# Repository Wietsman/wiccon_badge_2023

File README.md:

# Wiccon Badge 2023

# What is this repo: 
  This repo contains the source + firmware + PCB design for the WICCON 2023 Badge (https://wiccon.nl/) (not the SAO)

  Badge front:

  Badge back:

  The Folder PCB contains the main badge and the addon, created with KiCad.
  # Main badge
  ## Frontside
  * 4 WS2812B on the front. (made a mistake they are adressed counter clockwise)
  * 1 MODE button on the front to switch LED effects
  * 2 6 pin female connecter to attach the addon board (Cat and moon)
  * 1 SAO v1.69 (Shitty Addon) (https://hackaday.com/2019/03/20/introducing-the-shitty-add-on-v1-69bis-standard/)
  * |  PIN  |      Description      |
    |-------|-----------------------|
    | 3.3v  | Positive power supply |
    | GND   | Ground                |
    | SCL   | Not connected (sorry) |
    | SDA   | Not connected (sorry) |        
    | GPI12 | General-purpose pin   |
    | GPI13 | General-purpose pin   |    

## Backside
* ESP8622
* Powerswitch
* Reset button
* Flash button
* Batterybox
* stepdown converter (3.6-4.5v) to 3.3v
* couple of capacitor for WS2812B and stepdown converter
* 1 resistor
* lots of test pads so you can reuse the badge for other projects

## Schematic

## Usage
The badge has been designed to be reused for your project. The test pads can be used to solder anything to it and you can flash the ESP. 

You can use all the pads/pins except for (because i orderd the wrong ESP.....):
* MISO
* MOSI
* GPIO09
* GPIO10
* SCLK
* CSO

The following pins need are "special":
* GPIO00 pull to ground on boot to flash the ESP (or press flash button)
* GPIO15 is pulled to ground through a 10k resistor otherwise the ESP wont boot.

Flashing your own firmware, connect UART to tx/rx gnd power the device by battery or external 3.3v power. Hold the flash button, then press reset, release the flash button. Now you can flash your own firmware with esptool.py, arduino ide or what ever you want.

# Addon board
There are 2 addon boards for WICCON 2023, for guests (black cat and moon) and orga (purple moon, silver cat)
## Guestboard

## Orgaboard

## Schematic

## Backside

# Questions, remarks or whatever!

If you have any questions please drop me a message: 
* twitter: [twitter](https://twitter.com/wietsman)
* Website: [WBSEC.nl](https://www.wbsec.nl)

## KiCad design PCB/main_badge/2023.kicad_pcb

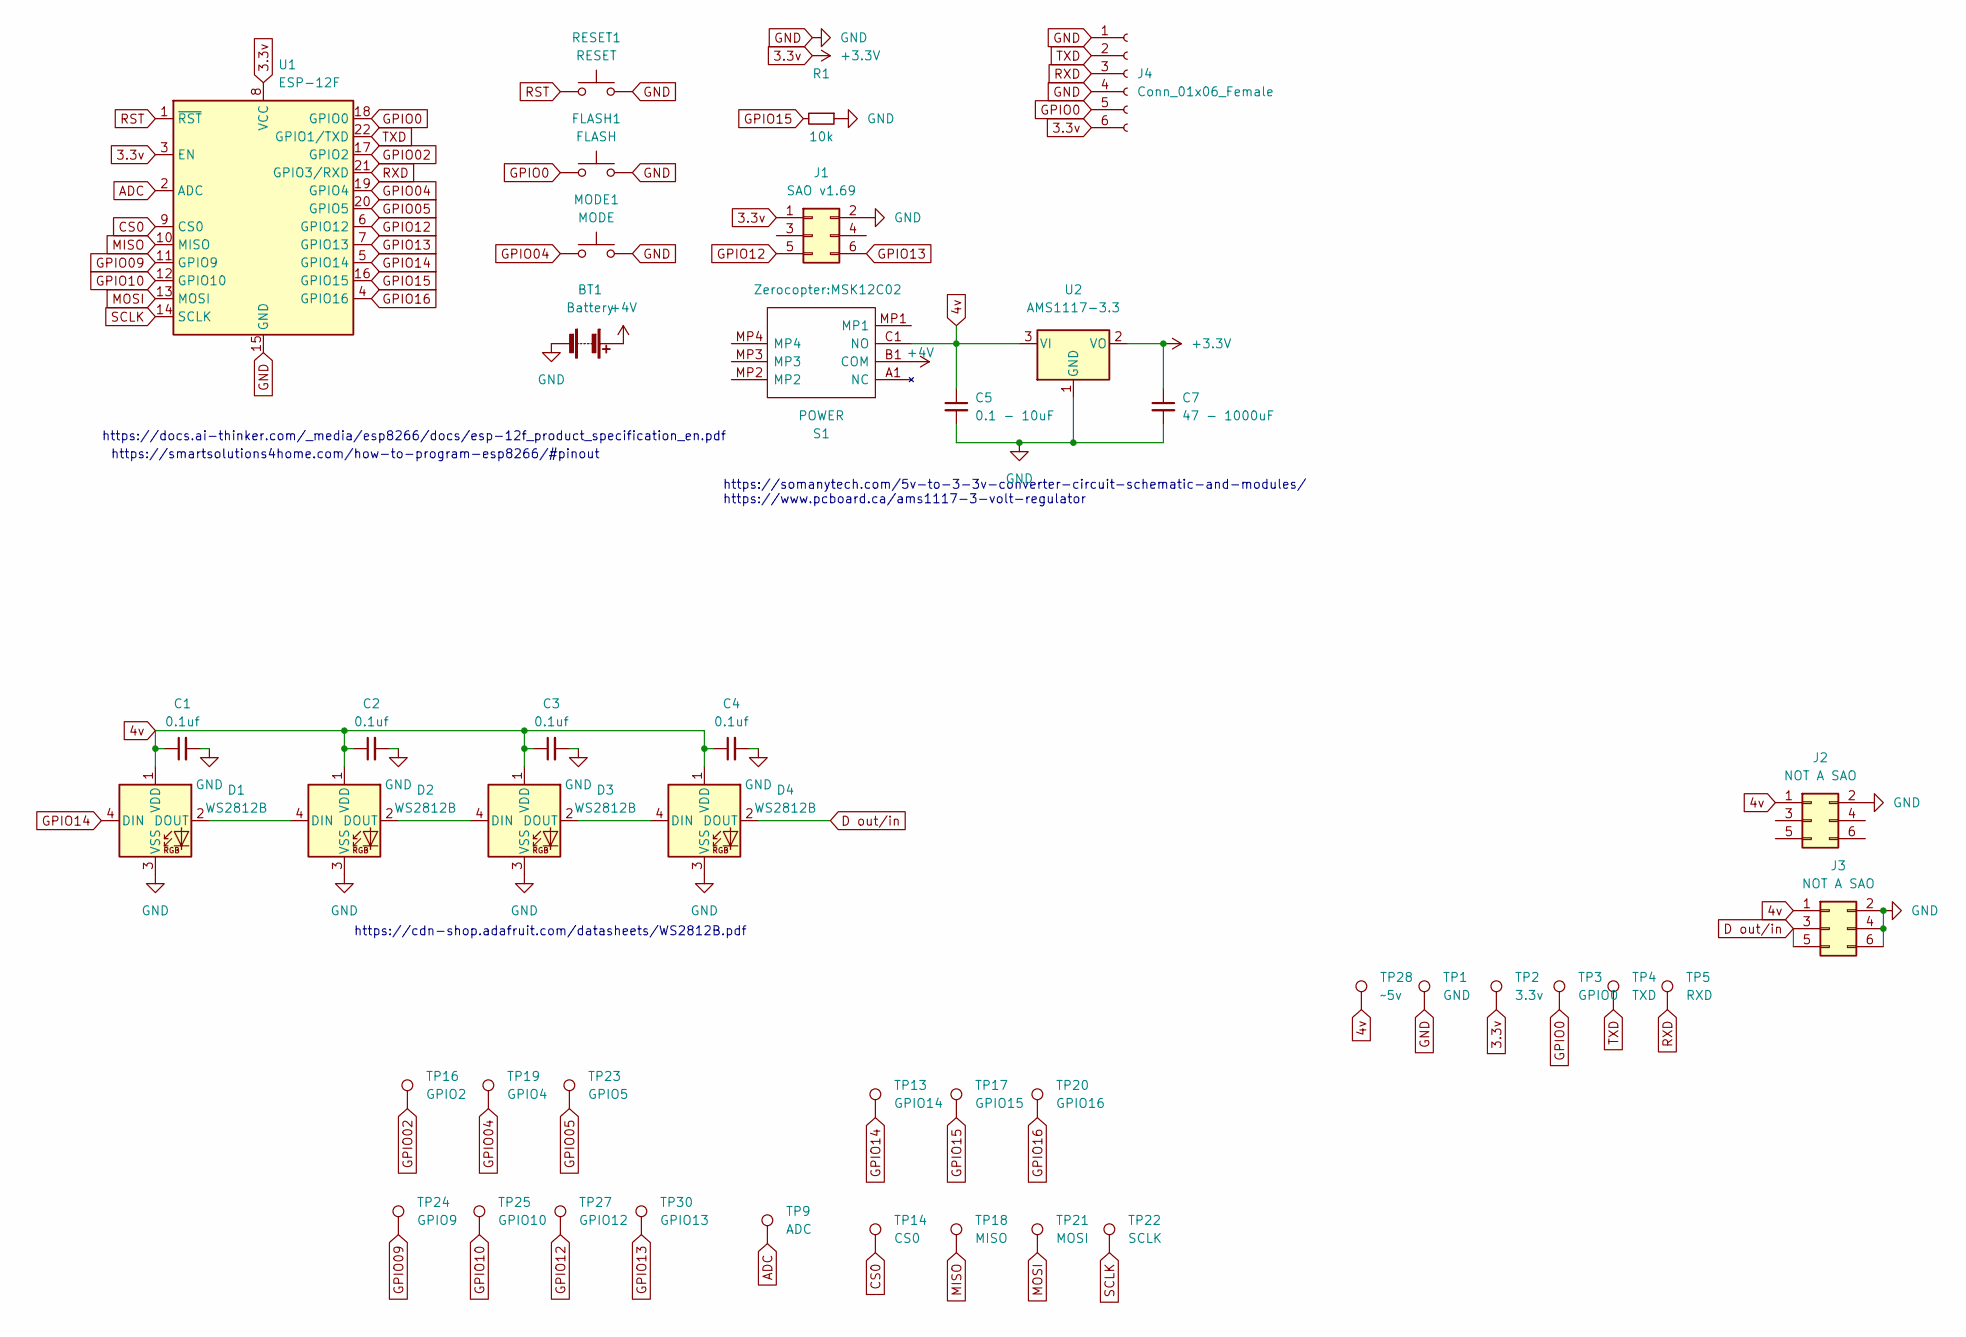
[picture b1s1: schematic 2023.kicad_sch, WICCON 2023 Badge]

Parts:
BT1: Battery; Battery_holder_3AA
C1, C2, C3, C4: 0.1uf; R_0805_2012Metric
C5: 0.1 - 10uF; C_0805_2012Metric_Pad1.18x1.45mm_HandSolder
C7: 47 - 1000uF; C_0805_2012Metric_Pad1.18x1.45mm_HandSolder
D1, D2, D3, D4: WS2812B; LED_WS2812B_PLCC4_5.0x5.0mm_P3.2mm
FLASH1: FLASH; sw_tactile_4x4
J1: SAO v1.69; PinSocket_2x03_P2.54mm_Vertical
J2, J3: NOT A SAO; PinSocket_2x03_P2.54mm_Vertical
J4: Conn_01x06_Female; Harting_har-flexicon_14110413010xxx_1x04-MP_P2.54mm_Horizon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
MODE1: MODE; sw_tactile_4x4
R1: 10k; R_0805_2012Metric_Pad1.20x1.40mm_HandSolder
RESET1: RESET; sw_tactile_4x4
S1: POWER; MSK12C02; Manufacturer_Part_Number MSK12C02
TP1: GND; TestPoint_Pad_4.0x4.0mm
TP2: 3.3v; TestPoint_Pad_4.0x4.0mm
TP3: GPIO0; TestPoint_Pad_4.0x4.0mm
TP4: TXD; TestPoint_Pad_4.0x4.0mm
TP5: RXD; TestPoint_Pad_4.0x4.0mm
TP9: ADC; TestPoint_Pad_4.0x4.0mm
TP13: GPIO14; TestPoint_Pad_4.0x4.0mm
TP14: CS0; TestPoint_Pad_4.0x4.0mm
TP16: GPIO2; TestPoint_Pad_4.0x4.0mm
TP17: GPIO15; TestPoint_Pad_4.0x4.0mm
TP18: MISO; TestPoint_Pad_4.0x4.0mm
TP19: GPIO4; TestPoint_Pad_4.0x4.0mm
TP20: GPIO16; TestPoint_Pad_4.0x4.0mm
TP21: MOSI; TestPoint_Pad_4.0x4.0mm
TP22: SCLK; TestPoint_Pad_4.0x4.0mm
TP23: GPIO5; TestPoint_Pad_4.0x4.0mm
TP24: GPIO9; TestPoint_Pad_4.0x4.0mm
TP25: GPIO10; TestPoint_Pad_4.0x4.0mm
TP27: GPIO12; TestPoint_Pad_4.0x4.0mm
TP28: ~5v; TestPoint_Pad_4.0x4.0mm
TP30: GPIO13; TestPoint_Pad_4.0x4.0mm
U1: ESP-12F; ESP-12E
U2: AMS1117-3.3; SOT-223-3_TabPin2

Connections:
3.3v: C7.1, J1.1, J4.6, TP2.1, U1.3 (EN), U1.8 (VCC), U2.2 (VO)
4v: C1.1, C2.1, C3.1, C4.1, C5.1, D1.1 (VDD), D2.1 (VDD), D3.1 (VDD), D4.1 (VDD), J2.1, J3.1, S1.C1 (NO), TP28.1, U2.3 (VI)
+4V: BT1.1 (+), S1.B1 (COM)
ADC: TP9.1, U1.2 (ADC)
CS0: TP14.1, U1.9 (CS0)
D out/in: D4.2 (DOUT), J3.3, J3.5
GND: BT1.2 (-), C1.2, C2.2, C3.2, C4.2, C5.2, C7.2, D1.3 (VSS), D2.3 (VSS), D3.3 (VSS), D4.3 (VSS), FLASH1.2, J1.2, J2.2, J3.2, J3.4, J3.6, J4.1, J4.4, MODE1.2, R1.1, RESET1.2, TP1.1, U1.15 (GND), U2.1 (GND)
GPIO0: FLASH1.1, J4.5, TP3.1, U1.18 (GPIO0)
GPIO02: TP16.1, U1.17 (GPIO2)
GPIO04: MODE1.1, TP19.1, U1.19 (GPIO4)
GPIO05: TP23.1, U1.20 (GPIO5)
GPIO09: TP24.1, U1.11 (GPIO9)
GPIO10: TP25.1, U1.12 (GPIO10)
GPIO12: J1.5, TP27.1, U1.6 (GPIO12)
GPIO13: J1.6, TP30.1, U1.7 (GPIO13)
GPIO14: D1.4 (DIN), TP13.1, U1.5 (GPIO14)
GPIO15: R1.2, TP17.1, U1.16 (GPIO15)
GPIO16: TP20.1, U1.4 (GPIO16)
MISO: TP18.1, U1.10 (MISO)
MOSI: TP21.1, U1.13 (MOSI)
unnamed: D1.2 (DOUT), D2.4 (DIN)
unnamed: D2.2 (DOUT), D3.4 (DIN)
unnamed: D3.2 (DOUT), D4.4 (DIN)
RST: RESET1.1, U1.1 (~RST)
RXD: J4.3, TP5.1, U1.21 (GPIO3/RXD)
SCLK: TP22.1, U1.14 (SCLK)
TXD: J4.2, TP4.1, U1.22 (GPIO1/TXD)

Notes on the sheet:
https://somanytech.com/5v-to-3-3v-converter-circuit-schematic-and-modules/ https://www.pcboard.ca/ams1117-3-volt-regulator
https://docs.ai-thinker.com/_media/esp8266/docs/esp-12f_product_specification_en.pdf
https://smartsolutions4home.com/how-to-program-esp8266/#pinout
https://cdn-shop.adafruit.com/datasheets/WS2812B.pdf

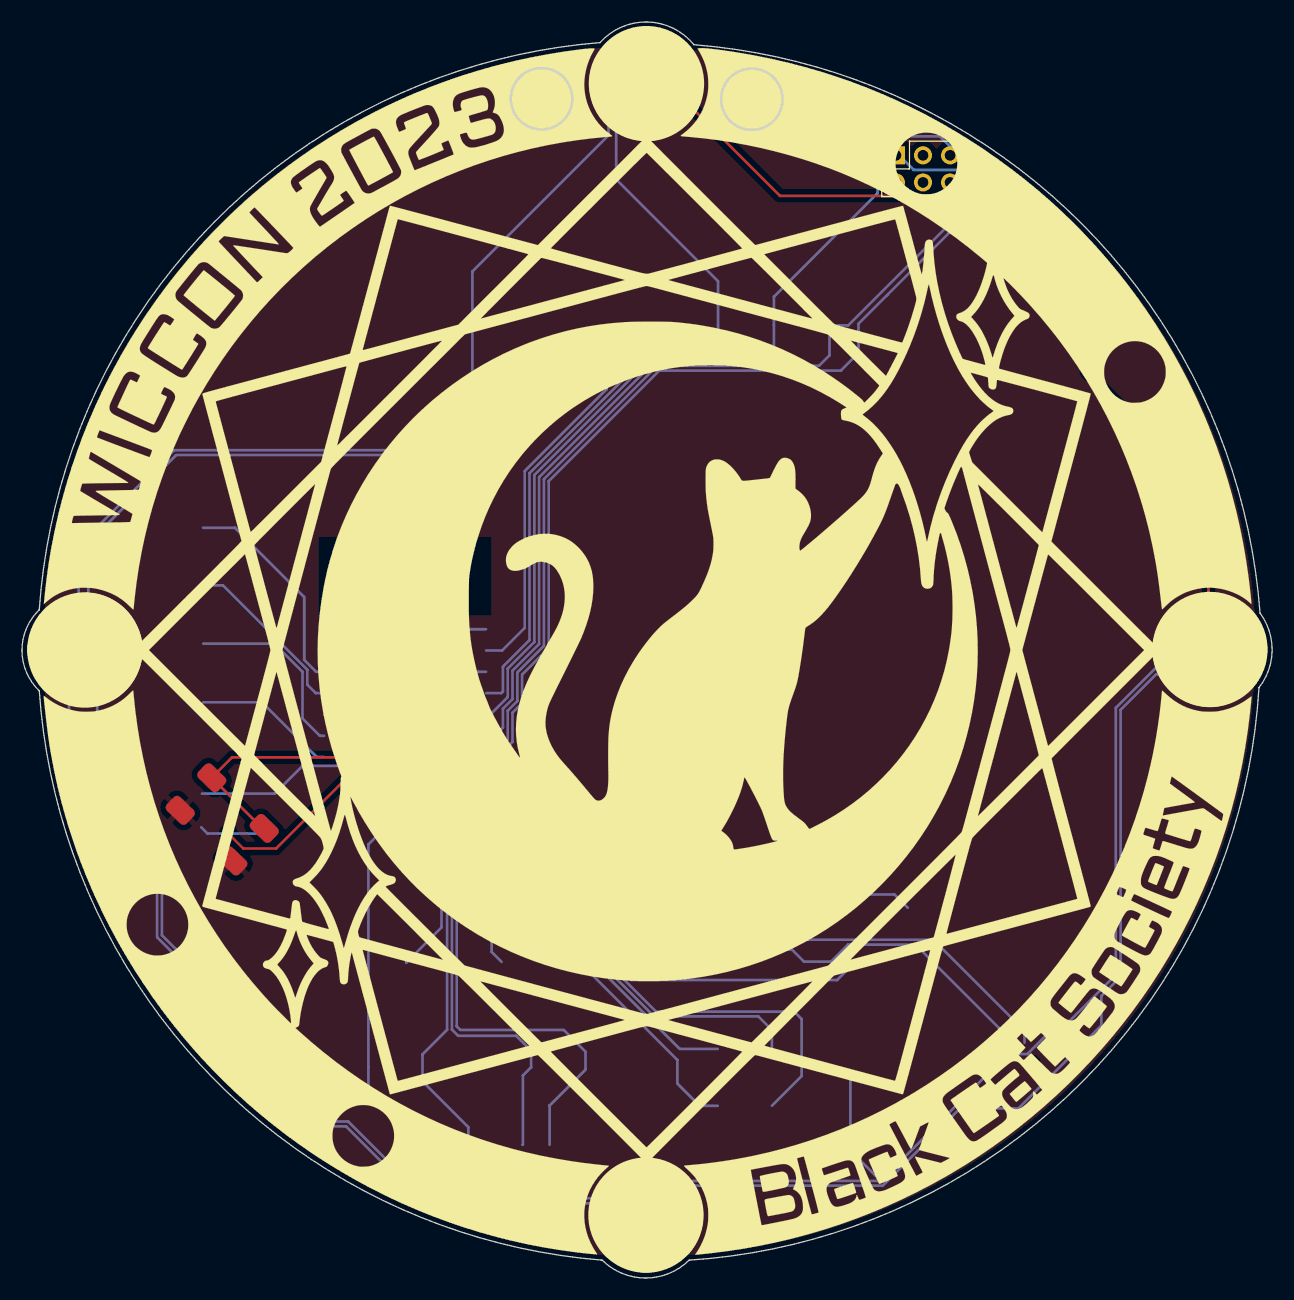
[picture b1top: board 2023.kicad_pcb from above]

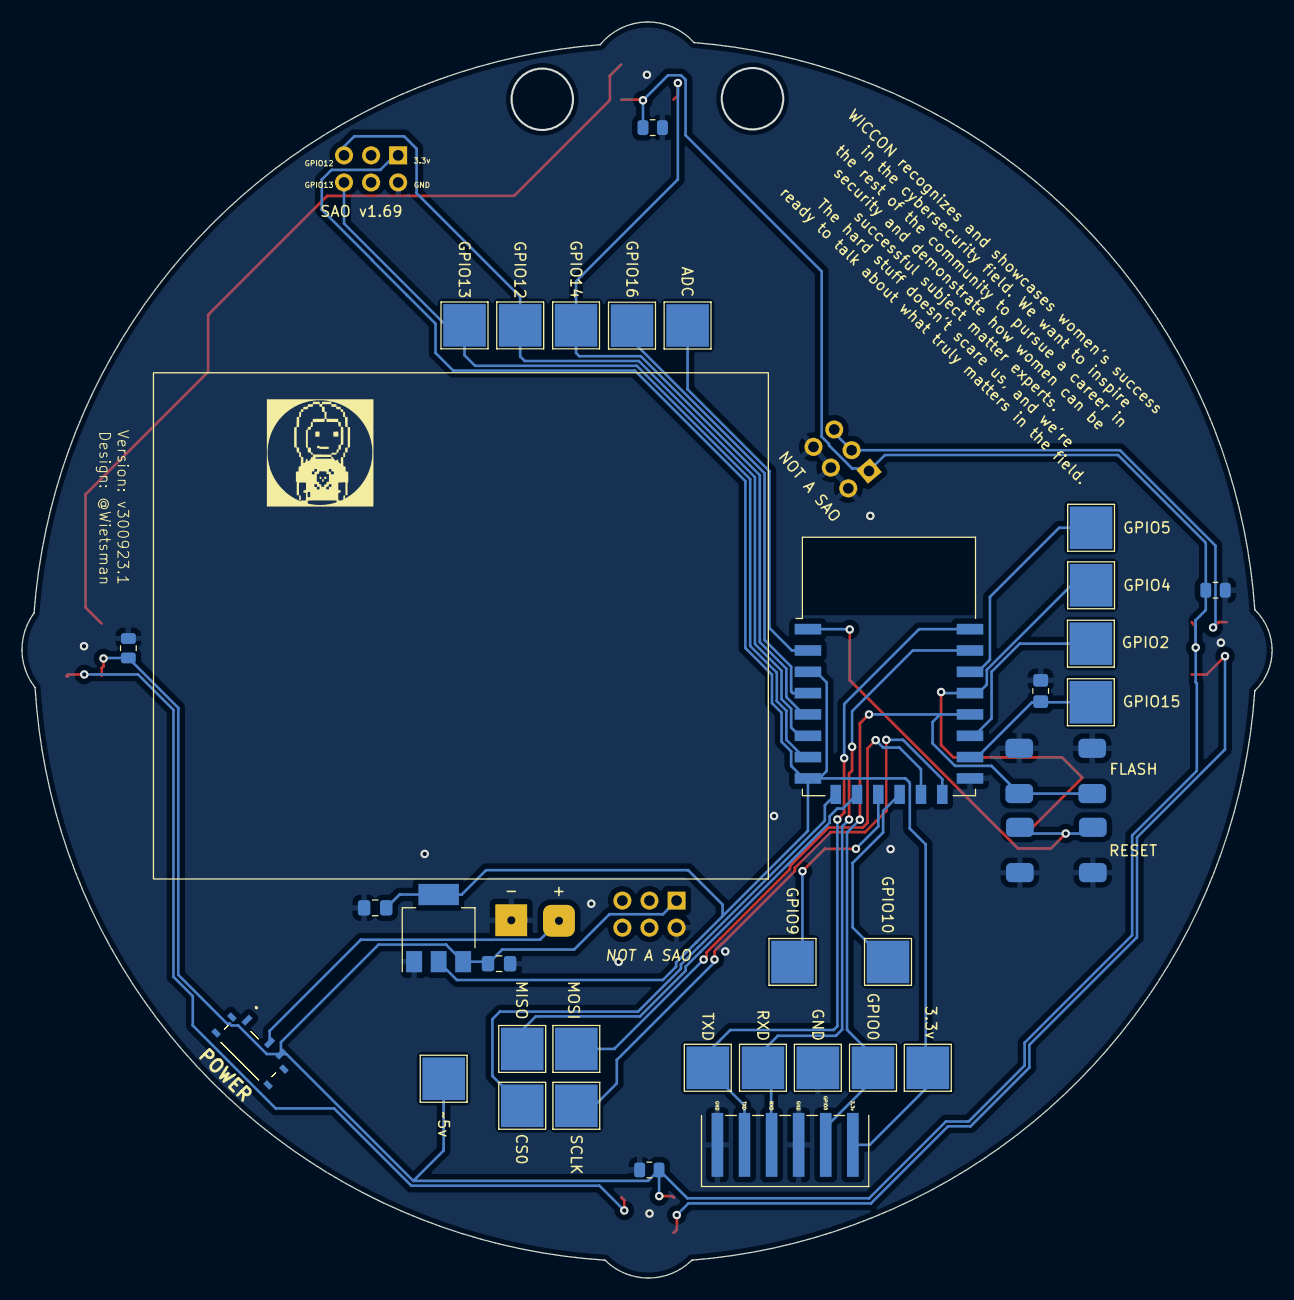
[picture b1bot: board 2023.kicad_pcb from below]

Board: 2 copper layers, 117.2 x 117.7 mm, 44 parts (35 on the bottom side), 27 nets.

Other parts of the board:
Ref**: Val**; WICCON_CAT_MOON_STAR2

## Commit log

2023-10-20 final release for Wiccon 2023
2023-10-20 first verion
2023-10-20 added image for readme.md
2023-10-20 updated .gitignore
2023-10-20 added images for README.MD
2023-10-20 changed README
2023-10-20 added more images of the badge
